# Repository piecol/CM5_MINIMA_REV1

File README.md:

# CM5_MINIMA_REV1
_Compact, feature-filled, CM5 LoRaWAN carrier board_

## **OSHWA**:
This project is certified as open-source hardware under the UID: IT000019
https://certification.oshwa.org/it000019.html

## **Warning**:
Board tested, everything works, except for the RAK3172 UART, which was moved from UART0_IR to UART2. It works with this change, schematics, layout and production files are corrected.

_Proceed at your own risk._

 [PDF SCHEMATICS](https://github.com/piecol/CM5_MINIMA_REV1/blob/main/CM5_MINIMA.pdf)

## **Peripherals**:
- USB-C PD (CM5 can negotiate power delivery!)
- USB2.0 
- Gigabit Ethernet with cutout magjack for low profile
- HDMI port
- RAK3172 lorawan chip from RAKwireless
- SHTC3 Sensirion temperature and humidity sensor
- I2C connector (3V3 only)
- Fan connector
- Various status LEDs
- Compact size 5.4 x 5.7 cm

## **Stackup**:
4L (SIG:PWR | GND | GND | SIG:PWR) 
JLC0416H-3313 impedance stackup

### If you would like to support me:

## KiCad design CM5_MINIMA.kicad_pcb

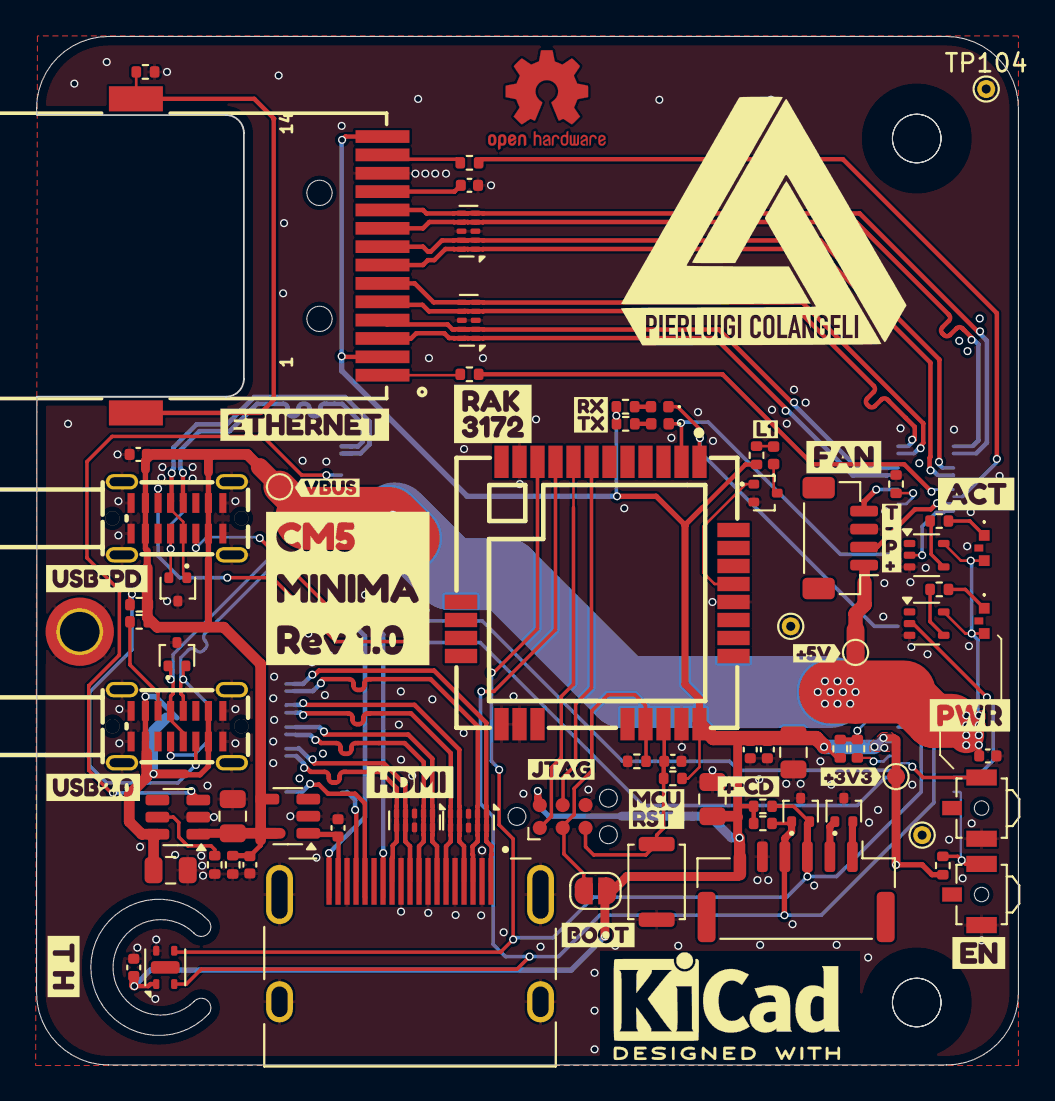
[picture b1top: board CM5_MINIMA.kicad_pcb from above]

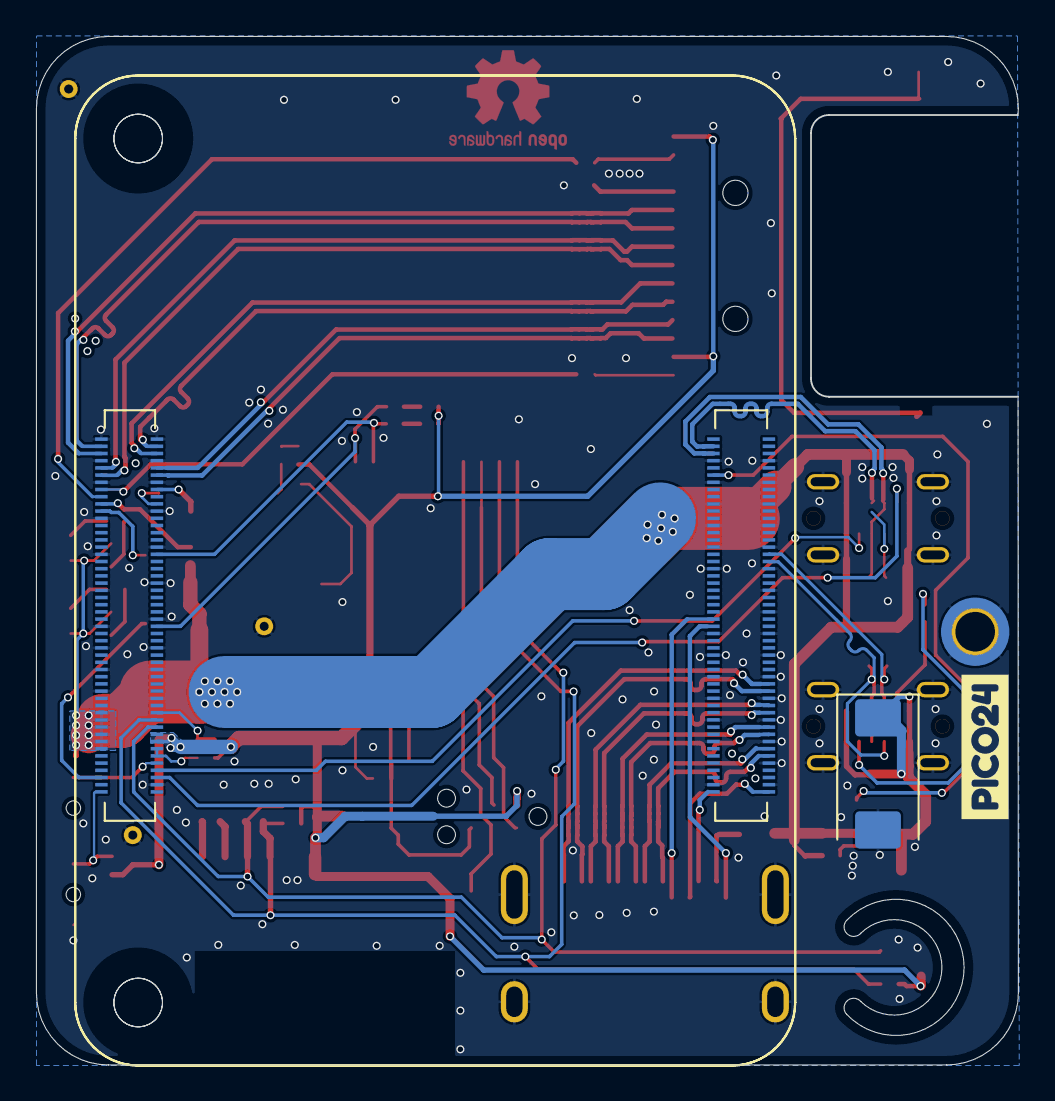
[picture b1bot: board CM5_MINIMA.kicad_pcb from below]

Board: 4 copper layers, 54.6 x 57.1 mm, 96 parts (4 on the bottom side), 69 nets.

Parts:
C101, C102, C401, C501, C502, C504, C505, C602: 100n; C_0402_1005Metric
C503, C601: 4u7; C_0805_2012Metric
C506: 100nF; C_0402_1005Metric
C701, C703: 10u; C_0805_2012Metric
C702: 100uF; CP_EIA-7343-31_Kemet-D
D101, D501, D502, D701: RCLAMP0502BA; SOT-416
D503, D504: CHRG; LED_0402_1005Metric
D505: LED; LED_0402_1005Metric
D605, D606: GREEN; Led_Wurth_0603_side
H101: MountingHole_Pad; MountingHole_2.2mm_M2_DIN965_Pad_TopBottom
J101: USB_C_Receptacle_USB2.0; USB-C-SMD_TYPEC-305-ACP16H458
J501: 690-019-298-412; EDAC 690-019-298-412
J502: I2C; JST_GH_BM06B-GHS-TBT_1x06-1MP_P1.25mm_Vertical
J601: JST_SHBM04B-SRSS-TB; JST_SH_BM04B-SRSS-TB_1x04-1MP_P1.00mm_Vertical
JP501: BOOT; SolderJumper-2_P1.3mm_Open_RoundedPad1.0x1.5mm
Module301: ComputeModule5-CM5; Raspberry-Pi-5-Compute-Module_GPIO
Module302: ComputeModule5-CM5; Raspberry-Pi-5-Compute-Module_HSS
Q501: DTC043ZEBTL; SOT-416
R101: 2.2K 1%; R_0402_1005Metric
R102, R403, R601: 0R; R_0402_1005Metric
R103: nf; R_0402_1005Metric
R104, R501, R502, R503, R504: 10k; R_0402_1005Metric
R401, R402: 470R; R_0402_1005Metric
R505, R506: 1k; R_0402_1005Metric
R507: 4k7; R_0402_1005Metric
R605, R606: 3k3; R_0402_1005Metric
R701: 15K 1%; R_0402_1005Metric
R702, R703: 22k; R_0402_1005Metric
SW501: SW_Push; SW_Push_SPST_NO_Alps_SKRK
SW601, SW602: B3U-3000P; SW_SPST_B3U-3100P-B
T401: 7498111120AR
TP101: VBUS; TestPoint_Pad_D1.0mm
TP102: +5V_PI; TestPoint_Pad_D1.0mm
TP103: +3V3_PI; TestPoint_Pad_D1.0mm
TP104, TP105, TP106: GND; TestPoint_THTPad_D1.0mm_Drill0.5mm
U401, U402, U403, U404: TPD4EUSB30; USON-10_2.5x1.0mm_P0.5mm
U405: STMPS2151STR; SOT-23-5
U502: RAK3172-8-SM-I; WIRELM-SMD_32P-L15.5-W15.0-P1.00
U503: Tag-Connect_TC2030-IDC-NL_2x03_P1.27mm_Vertical
U601: SHTC3; Sensirion_DFN-4-1EP_2x2mm_P1mm_EP0.7x1.6mm
U602, U603: 74LVC1G07SE-7; SOT-353_SC-70-5
U701: AP22653W6; SOT-23-6
USB701: TYPEC-305-ACP16H458; USB-C-SMD_TYPEC-305-ACP16H458
kibuzzard-675DA85E: G***; kibuzzard-675DA85E
kibuzzard-675DA838: G***; kibuzzard-675DA838
kibuzzard-675DA850: G***; kibuzzard-675DA850
kibuzzard-675DA866: G***; kibuzzard-675DA866
kibuzzard-675DB3C2: G***; kibuzzard-675DB3C2
kibuzzard-675DBE31: G***; kibuzzard-675DBE31
kibuzzard-675DBE43: G***; kibuzzard-675DBE43
kibuzzard-675DC2F1: G***; kibuzzard-675DC2F1
kibuzzard-675DCF7A: G***; kibuzzard-675DCF7A
kibuzzard-675DCF9A: G***; kibuzzard-675DCF9A
kibuzzard-675DF4E5: G***; kibuzzard-675DF4E5
kibuzzard-675EDCA4: G***; kibuzzard-675EDCA4
kibuzzard-675EDCB9: G***; kibuzzard-675EDCB9
kibuzzard-67601A65: G***; kibuzzard-67601A65
kibuzzard-67601AC8: G***; kibuzzard-67601AC8
kibuzzard-67601C98: G***; kibuzzard-67601C98
kibuzzard-67602DFF: G***; kibuzzard-67602DFF
kibuzzard-676020C0: G***; kibuzzard-676020C0
kibuzzard-676020D8: G***; kibuzzard-676020D8
kibuzzard-676020F6: G***; kibuzzard-676020F6
kibuzzard-67601717: G***; kibuzzard-67601717
kibuzzard-67602076: G***; kibuzzard-67602076

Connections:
+1V8: Module301.88 (+1.8v_(Output)), Module301.90 (+1.8v_(Output)), R103.1
+3V3: C503.1, C504.1, C505.1, C601.1, C602.1, J502.6, JP501.2 (B), Module301.84 (+3.3v_(Output)), Module301.86 (+3.3v_(Output)), R102.1, R501.1, R502.1, R504.1, R505.1, R506.1, R507.1, R601.1, T401.2, T401.14, TP103.1, U502.24 (VDD), U503.2 (VCC), U601.1 (VDD)
+5V: C101.1, C102.1, C501.1, C701.1, D605.2 (A), D606.2 (A), J101.A4 (VBUS), J101.A9 (VBUS), J101.B4 (VBUS), J101.B9 (VBUS), J601.1, Module301.77 (+5v_(Input)), Module301.79 (+5v_(Input)), Module301.81 (+5v_(Input)), Module301.83 (+5v_(Input)), Module301.85 (+5v_(Input)), Module301.87 (+5v_(Input)), R101.1, R702.2, R703.2, TP101.1, TP102.1, U405.4 (EN), U405.5 (VIN), U602.5 (VCC), U603.5 (VCC), U701.1 (IN)
/CC1: J101.A5 (CC1), Module301.94 (CC1)
/CC2: J101.B5 (CC2), Module301.96 (CC2)
/CM5/EEPROM_nWP: Module301.20 (EEPROM_nWP), R104.2
/CM5/ETH_PI.TRD0_N: Module301.10 (Ethernet_Pair0_N), T401.4 (D1-), U401.2 (D1-), U401.9
/CM5/ETH_PI.TRD0_P: Module301.12 (Ethernet_Pair0_P), T401.3 (D1+), U401.1 (D1+), U401.10
/CM5/ETH_PI.TRD1_N: Module301.6 (Ethernet_Pair1_N), T401.6 (D2-), U401.5 (D2-), U401.6
/CM5/ETH_PI.TRD1_P: Module301.4 (Ethernet_Pair1_P), T401.5 (D2+), U401.4 (D2+), U401.7
/CM5/ETH_PI.TRD2_N: Module301.9 (Ethernet_Pair2_N), T401.8 (D3-), U402.2 (D1-), U402.9
/CM5/ETH_PI.TRD2_P: Module301.11 (Ethernet_Pair2_P), T401.7 (D3+), U402.1 (D1+), U402.10
/CM5/ETH_PI.TRD3_N: Module301.5 (Ethernet_Pair3_N), T401.10 (D4-), U402.5 (D2-), U402.6
/CM5/ETH_PI.TRD3_P: Module301.3 (Ethernet_Pair3_P), T401.9 (D4+), U402.4 (D2+), U402.7
/CM5/ETH_nLED_ACTIVITY: Module301.15 (Ethernet_nLED3(3.3v)), R401.1
/CM5/GLOBAL_EN: Module301.99 (PMIC_ENABLE), R601.2, SW601.1
/CM5/GPIO_VREF: Module301.78 (GPIO_VREF(1.8v/3.3v_Input)), R102.2, R103.2
/CM5/HDMI_PI.HDMI0_CEC: J501.13 (CEC), Module302.151 (HDMI0_CEC)
/CM5/HDMI_PI.HDMI0_CK_N: J501.12 (CK-), Module302.190 (HDMI0_CLK_N), U404.5 (D2-), U404.6
/CM5/HDMI_PI.HDMI0_CK_P: J501.10 (CK+), Module302.188 (HDMI0_CLK_P), U404.4 (D2+), U404.7
/CM5/HDMI_PI.HDMI0_D0_N: J501.9 (D0-), Module302.184 (HDMI0_TX0_N), U404.2 (D1-), U404.9
/CM5/HDMI_PI.HDMI0_D0_P: J501.7 (D0+), Module302.182 (HDMI0_TX0_P), U404.1 (D1+), U404.10
/CM5/HDMI_PI.HDMI0_D1_N: J501.6 (D1-), Module302.178 (HDMI0_TX1_N), U403.5 (D2-), U403.6
/CM5/HDMI_PI.HDMI0_D1_P: J501.4 (D1+), Module302.176 (HDMI0_TX1_P), U403.4 (D2+), U403.7
/CM5/HDMI_PI.HDMI0_D2_N: J501.3 (D2-), Module302.172 (HDMI0_TX2_N), U403.2 (D1-), U403.9
/CM5/HDMI_PI.HDMI0_D2_P: J501.1 (D2+), Module302.170 (HDMI0_TX2_P), U403.1 (D1+), U403.10
/CM5/HDMI_PI.HDMI0_HOTPLUG: J501.19 (HPD/HEAC-), Module302.153 (HDMI0_HOTPLUG)
/CM5/HDMI_PI.HDMI0_SCL: J501.15 (SCL), Module302.200 (HDMI0_SCL)
/CM5/HDMI_PI.HDMI0_SDA: J501.16 (SDA), Module302.199 (HDMI0_SDA)
/CM5/PI_nLED_PWR: Module301.95 (LED_nPWR), U602.2
/CM5/PWM: J601.2, Module301.19 (FAN_PWM)
/CM5/PWR_BUT: Module301.92 (PWR_BUT), SW602.1
/CM5/TACHO: J601.4, Module301.16 (FAN_TACHO)
/CM5/USB2P.D_N: D701.2 (K2), Module302.136 (USB3-0-D_N), USB701.A7 (D-), USB701.B7 (D-)
/CM5/USB2P.D_P: D701.1 (K1), Module302.134 (USB3-0-D_P), USB701.A6 (D+), USB701.B6 (D+)
/CM5/VBUS_EN: Module302.111 (VBUS_EN), U701.3 (EN)
/CM5/nLED_ACTIVITY: Module301.21 (LED_nACT), U603.2
/CM5/nLED_SPEED_100_1000: Module301.17 (Ethernet_nLED2(3.3v)), R402.1
/HDMI/HDMI_5v: C502.1, J501.18 (+5V), U405.1 (VOUT)
/IO/IO5: D501.1 (K1), J502.2
/IO/IO6: D501.2 (K2), J502.1
/LoRaWAN/BOOT: JP501.1 (A), R503.1, U502.21 (BOOT0), U503.3 (BOOT)
/LoRaWAN/LED1: Q501.1 (B), U502.29 (PA0)
/LoRaWAN/RAK_RST: C506.1, R504.2, SW501.2, U502.22 (RST), U503.5 (~RESET)
/LoRaWAN/SWCLK: U502.8 (PA14/SWCLK), U503.1 (SWCLK)
/LoRaWAN/SWDIO: U502.7 (PA13/SWDIO), U503.4 (SWDIO)
/LoRaWAN/UART2_RX: D503.1 (K), Module301.54 (GPIO4), U502.1 (PA3/UART2_RX)
/LoRaWAN/UART2_TX: D504.1 (K), Module301.34 (GPIO5), U502.2 (PA2/UART2_TX)
/SCL: D502.1 (K1), J502.4, Module301.80 (SCL0), R502.2, U502.9 (PA12/I2C_SCL), U601.2 (SCL)
/SDA: D502.2 (K2), J502.3, Module301.82 (SDA0), R501.2, U502.10 (PA11/I2C_SDA), U601.3 (SDA)
/USB/CC1: R703.1, USB701.A5 (CC1)
/USB/CC2: R702.1, USB701.B5 (CC2)
/USB/VBUS: C702.1, C703.1, U701.6 (OUT), USB701.A4 (VBUS), USB701.A9 (VBUS), USB701.B4 (VBUS), USB701.B9 (VBUS)
/USB_C.D_N: D101.2 (K2), J101.A7 (D-), J101.B7 (D-), Module302.103 (USB2_N)
/USB_C.D_P: D101.1 (K1), J101.A6 (D+), J101.B6 (D+), Module302.105 (USB2_P)
GND: C101.2, C102.2, C401.2, C501.2, C502.2, C503.2, C504.2, C505.2, C506.2, C601.2, C602.2, C701.2, C702.2, C703.2, D101.3 (A), D501.3 (A), D502.3 (A), D701.3 (A), H101.1, J101.1 (SHIELD), J101.A1 (GND), J101.A12 (GND), J101.B1 (GND), J101.B12 (GND), J501.2 (D2S), J501.5 (D1S), J501.8 (D0S), J501.11 (CKS), J501.17 (GND), J501.SH1 (SH), J501.SH2 (SH), J501.SH3 (SH), J501.SH4 (SH), J502.5, J601.3, Module301.1 (GND), Module301.2 (GND), Module301.7 (GND), Module301.8 (GND), Module301.13 (GND), Module301.14 (GND), Module301.22 (GND), Module301.23 (GND), Module301.32 (GND), Module301.33 (GND), Module301.42 (GND), Module301.43 (GND), Module301.52 (GND), Module301.53 (GND), Module301.59 (GND), Module301.60 (GND), Module301.65 (GND), Module301.66 (GND), Module301.71 (GND), Module301.74 (GND), Module301.98 (GND), Module302.107 (GND), Module302.108 (GND), Module302.113 (GND), Module302.114 (GND), Module302.119 (GND), Module302.120 (GND), Module302.125 (GND), Module302.126 (GND), Module302.131 (GND), Module302.132 (GND), Module302.137 (GND), Module302.138 (GND), Module302.144 (GND), Module302.150 (GND), Module302.155 (GND), Module302.156 (GND), Module302.161 (GND), Module302.162 (GND), Module302.167 (GND), Module302.168 (GND), Module302.173 (GND), Module302.174 (GND), Module302.179 (GND), Module302.180 (GND), Module302.185 (GND), Module302.186 (GND), Module302.191 (GND), Module302.192 (GND), Module302.197 (GND), Module302.198 (GND), Q501.2 (E), R101.2, R104.1, R403.2, R503.2, R701.2, SW501.1, SW601.2, SW602.2, T401.12 (GND), TP104.1, TP105.1, TP106.1, U401.3 (GND), U401.8 (GND), U402.3 (GND), U402.8 (GND), U403.3 (GND), U403.8 (GND), U404.3 (GND), U404.8 (GND), U405.2 (GND), U502.11 (GND), U502.17 (GND), U502.18 (GND), U502.23 (GND), U502.28 (GND), U503.6 (GND), U601.4 (VSS), U602.3 (GND), U603.3 (GND), U701.2 (GND), USB701.1 (EP), USB701.A1 (GND), USB701.A12 (GND), USB701.B1 (GND), USB701.B12 (GND)
unnamed: D503.2 (A), R505.2
unnamed: D504.2 (A), R506.2
unnamed: D505.2 (A), R507.2
unnamed: D505.1 (K), Q501.3 (C)
unnamed: D605.1 (K), R605.1
unnamed: D606.1 (K), R606.1
unnamed: R401.2, T401.1
unnamed: R402.2, T401.13
unnamed: R605.2, U602.4
unnamed: R606.2, U603.4
unnamed: R403.1, T401.S1 (SHIELD1), T401.S2 (SHIELD2)
unnamed: C401.1, T401.11 (VCC)
unnamed: R701.1, U701.5 (ILIM)

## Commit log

2024-12-17 DRC ok
2024-12-17 round slot TH
2024-12-17 pics added
2024-12-17 changed switch on HDMI
2024-12-17 bom finished
2024-12-17 fix problem ethernet connector
2024-12-17 production files added
2024-12-17 removed old prod files
2024-12-18 save exit
2024-12-21 JLCPCB
2024-12-21 init
2024-12-21 diff pairs redesigned for pcbway capabilities
2024-12-22 impedance PCBway
2025-01-04 save close
2025-01-10 RAK3172 from UART0_IR to UART3
2025-01-10 RAK to UART2 PCB
2025-01-10 updated PCBWay fab files
2025-01-10 PDF schematics updated
